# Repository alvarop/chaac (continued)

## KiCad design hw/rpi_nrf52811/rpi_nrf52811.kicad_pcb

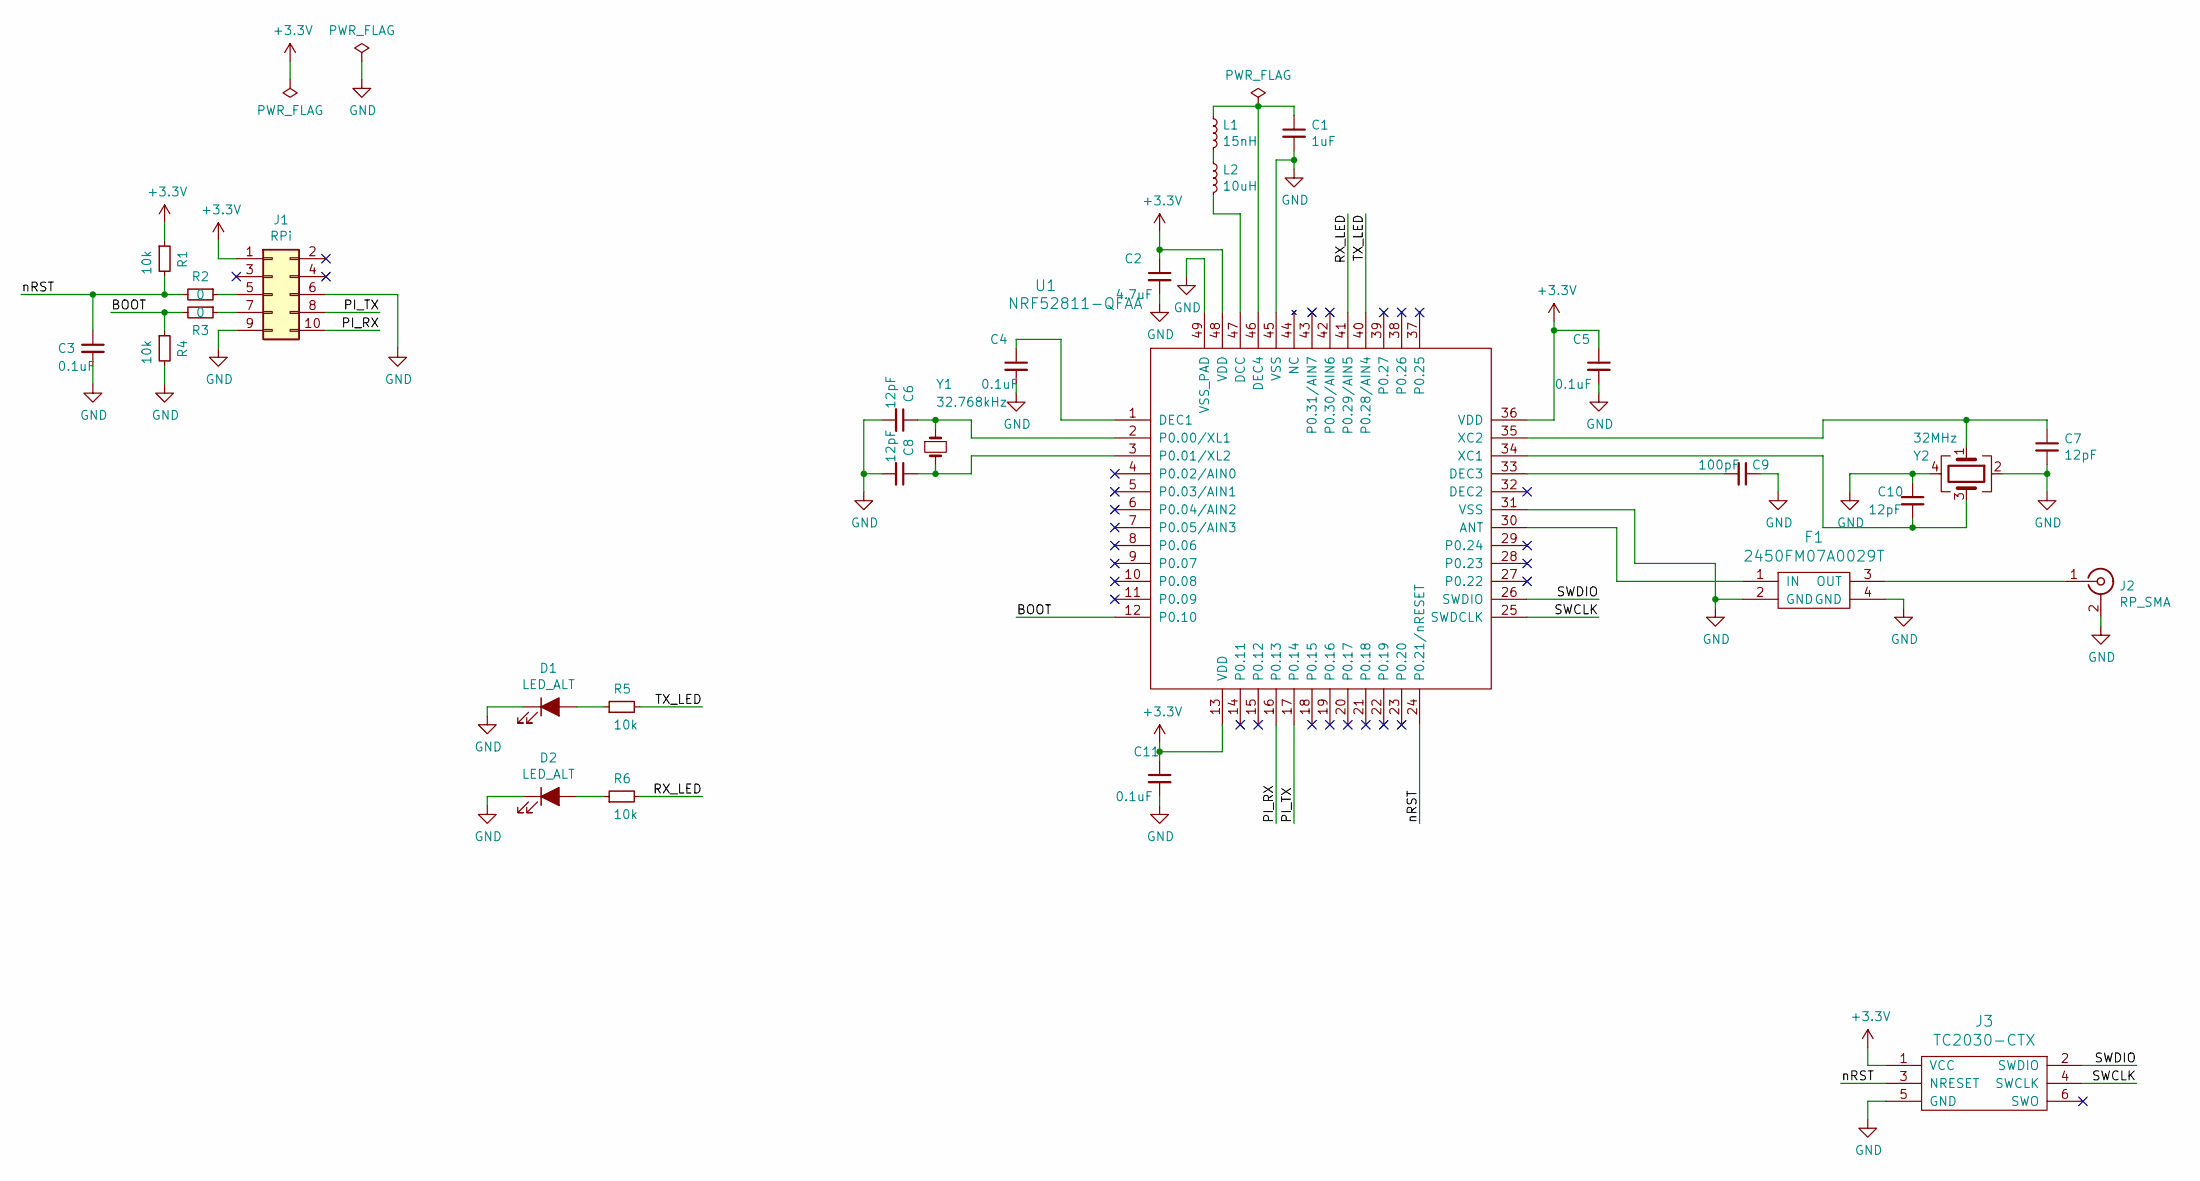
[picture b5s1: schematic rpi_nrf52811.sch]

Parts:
C1: 1uF; C_0402_1005Metric; MPN CC0402KRX5R5BB105
C2: 4.7uF; C_0603_1608Metric; MPN CL10B475KQ8NQNC
C3, C4, C5, C11: 0.1uF; C_0402_1005Metric; MPN GRM155R61A104KA01D
C6, C7, C8, C10: 12pF; C_0402_1005Metric; MPN C0402C120J5GACTU
C9: 100pF; C_0402_1005Metric; MPN UMK105CG101JV-F
D1, D2: LED_ALT; LED_0402_1005Metric; MPN QBLP595-IG
F1: 2450FM07A0029T; MPN 2450FM07A0029T
J1: RPi; PinSocket_2x05_P2.54mm_Vertical_SMD; MPN NPPC052KFMS-RC
J2: RP_SMA; SMA_Samtec_SMA-J-P-H-ST-EM1_EdgeMount; MPN CONREVSMA003.062
J3: TC2030-CTX; TC2030-NL
L1: 15nH; L_0402_1005Metric; MPN HK100515NJ-T‎
L2: 10uH; L_0603_1608Metric; MPN ‎LQM18FN100M00D‎
R1, R4, R5, R6: 10k; R_0402_1005Metric; MPN RC0402JR-0710KL
R2, R3: 0; R_0402_1005Metric; MPN RC1005J000CS
U1: NRF52811-QFAA; NRF52811-QFN48; MPN ‎NRF52811-QFAA-R‎
Y1: 32.768kHz; Crystal_SMD_3215-2Pin_3.2x1.5mm; MPN FC-135 32.7680KA-AC0
Y2: 32MHz; Crystal_SMD_2016-4Pin_2.0x1.6mm; MPN CX2016DB32000D0FLJCC

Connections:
+3V3: C2.1, C5.1, C11.1, J1.1, J3.1 (VCC), R1.1, U1.13 (VDD), U1.36 (VDD), U1.48 (VDD)
/BOOT: R3.2, R4.1, U1.12 (P0.10)
/PI_RX: J1.10, U1.16 (P0.13)
/PI_TX: J1.8, U1.17 (P0.14)
/RX_LED: R6.2, U1.41 (P0.29/AIN5)
/SWCLK: J3.4 (SWCLK), U1.25 (SWDCLK)
/SWDIO: J3.2 (SWDIO), U1.26 (SWDIO)
/TX_LED: R5.2, U1.40 (P0.28/AIN4)
/nRST: C3.1, J3.3 (NRESET), R1.2, R2.2, U1.24 (P0.21/nRESET)
GND: C1.2, C2.2, C3.2, C4.2, C5.2, C6.2, C7.2, C8.2, C9.1, C10.1, C11.2, D1.1 (K), D2.1 (K), F1.2 (GND), F1.4 (GND), J1.6, J1.9, J2.2 (Ext), J3.5 (GND), R4.2, U1.31 (VSS), U1.45 (VSS), U1.49 (VSS_PAD), Y2.2, Y2.4
unnamed: C1.1, L1.1, U1.46 (DEC4)
unnamed: C4.1, U1.1 (DEC1)
unnamed: C6.1, U1.2 (P0.00/XL1), Y1.1
unnamed: C7.1, U1.35 (XC2), Y2.1
unnamed: C8.1, U1.3 (P0.01/XL2), Y1.2
unnamed: C9.2, U1.33 (DEC3)
unnamed: C10.2, U1.34 (XC1), Y2.3
unnamed: D1.2 (A), R5.1
unnamed: D2.2 (A), R6.1
unnamed: F1.1 (IN), U1.30 (ANT)
unnamed: F1.3 (OUT), J2.1 (In)
unnamed: J1.5, R2.1
unnamed: J1.7, R3.1
unnamed: L1.2, L2.1
unnamed: L2.2, U1.47 (DCC)

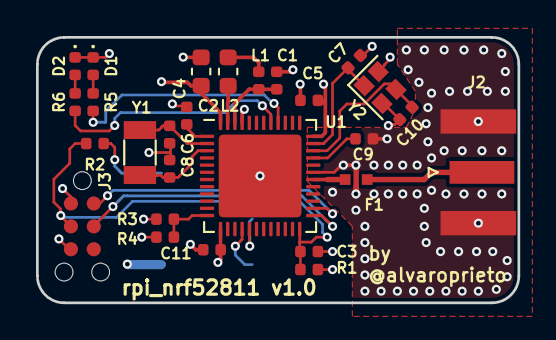
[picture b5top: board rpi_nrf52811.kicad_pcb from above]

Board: 4 copper layers, 26.8 x 14.8 mm, 28 parts (1 on the bottom side), 25 nets.

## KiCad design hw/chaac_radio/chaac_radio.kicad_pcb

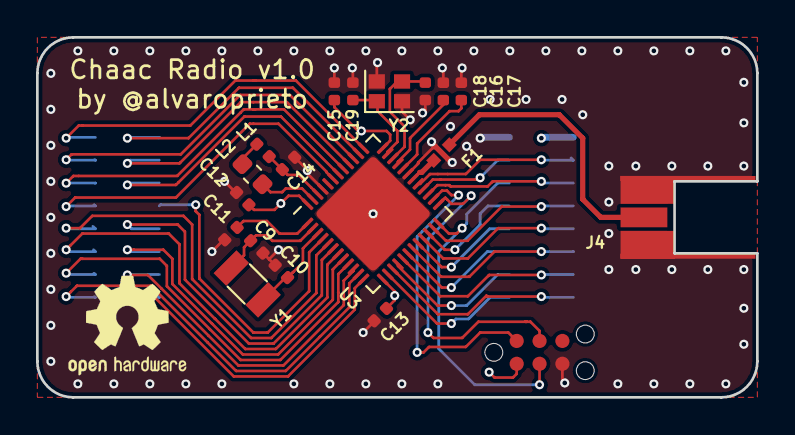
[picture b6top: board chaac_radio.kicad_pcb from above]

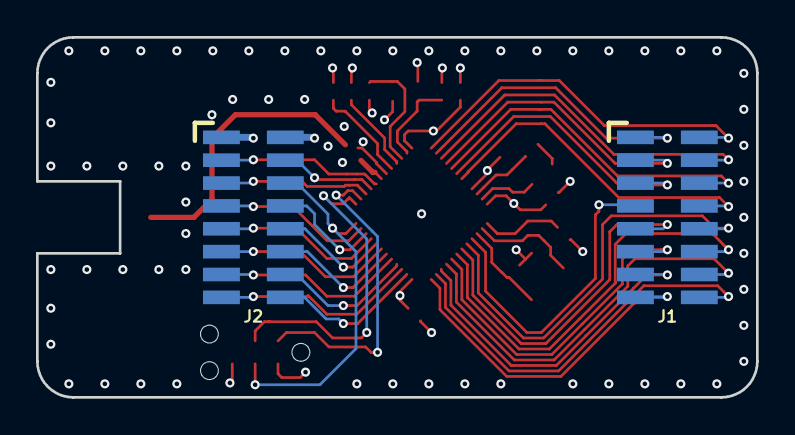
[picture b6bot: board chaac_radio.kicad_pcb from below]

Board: 4 copper layers, 40.0 x 20.0 mm, 21 parts (2 on the bottom side), 46 nets.

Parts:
C9, C10, C18, C19: 12pF; C_0402_1005Metric
C11, C13, C15: 0.1uF; C_0402_1005Metric
C12: 4.7uF; C_0402_1005Metric
C14: 1uF; C_0402_1005Metric
C16: 100pF; C_0402_1005Metric
C17: DNP; C_0402_1005Metric
F1: 2450FM07A0029T
J1, J2: 20021321-00016C4LF
J3: TC2030-CTX; TC2030-NL
J4: RP_SMA; MOLEX-0734150963
L1: 15nH; L_0402_1005Metric
L2: 10uH; L_0603_1608Metric
U3: NRF52811-QFAA; QFN-48-1EP_6x6mm_P0.4mm_EP4.6x4.6mm
Y1: 32.768kHz; Crystal_SMD_3215-2Pin_3.2x1.5mm
Y2: 32MHz; Crystal_SMD_2016-4Pin_2.0x1.6mm

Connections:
+3V3: C12.1, C13.1, C15.1, J2.1, J3.1, U3.13, U3.36, U3.48
/P0.02-AIN0: J1.7, U3.4
/P0.03-AIN1: J1.10, U3.5
/P0.04-AIN2: J1.9, U3.6
/P0.05-AIN3: J1.12, U3.7
/P0.06: J1.11, U3.8
/P0.07: J1.14, U3.9
/P0.08: J1.13, U3.10
/P0.09: J1.16, U3.11
/P0.10: J1.15, U3.12
/P0.11: J2.16, U3.14
/P0.12: J2.15, U3.15
/P0.13: J2.14, U3.16
/P0.14: J2.13, U3.17
/P0.15: J2.12, U3.18
/P0.16: J2.11, U3.19
/P0.17: J2.10, U3.20
/P0.18: J2.9, U3.21
/P0.19: J2.8, U3.22
/P0.20: J2.7, U3.23
/P0.22: J2.5, U3.27
/P0.23: J2.4, U3.28
/P0.24: J2.3, U3.29
/P0.25: J1.2, U3.37
/P0.26: J1.1, U3.38
/P0.27: J1.4, U3.39
/P0.28-AIN4: J1.3, U3.40
/P0.29-AIN5: J1.6, U3.41
/P0.30-AIN6: J1.5, U3.42
/P0.31-AIN7: J1.8, U3.43
/SWCLK: J3.4, U3.25
/SWDIO: J3.2, U3.26
/nRST: J2.6, J3.3, U3.24
GND: C9.2, C10.2, C11.2, C12.2, C13.2, C14.2, C15.2, C16.1, C17.1, C18.1, C19.2, F1.2, F1.4, J2.2, J3.5, J4.2, U3.31, U3.45, U3.49, Y2.2, Y2.4
unnamed: C9.1, U3.2, Y1.1
unnamed: C10.1, U3.3, Y1.2
unnamed: C11.1, U3.1
unnamed: C14.1, L1.1, U3.46
unnamed: C16.2, U3.33
unnamed: C17.2, U3.32
unnamed: C18.2, U3.34, Y2.3
unnamed: C19.1, U3.35, Y2.1
unnamed: F1.1, U3.30
unnamed: F1.3, J4.1
unnamed: L1.2, L2.1
unnamed: L2.2, U3.47

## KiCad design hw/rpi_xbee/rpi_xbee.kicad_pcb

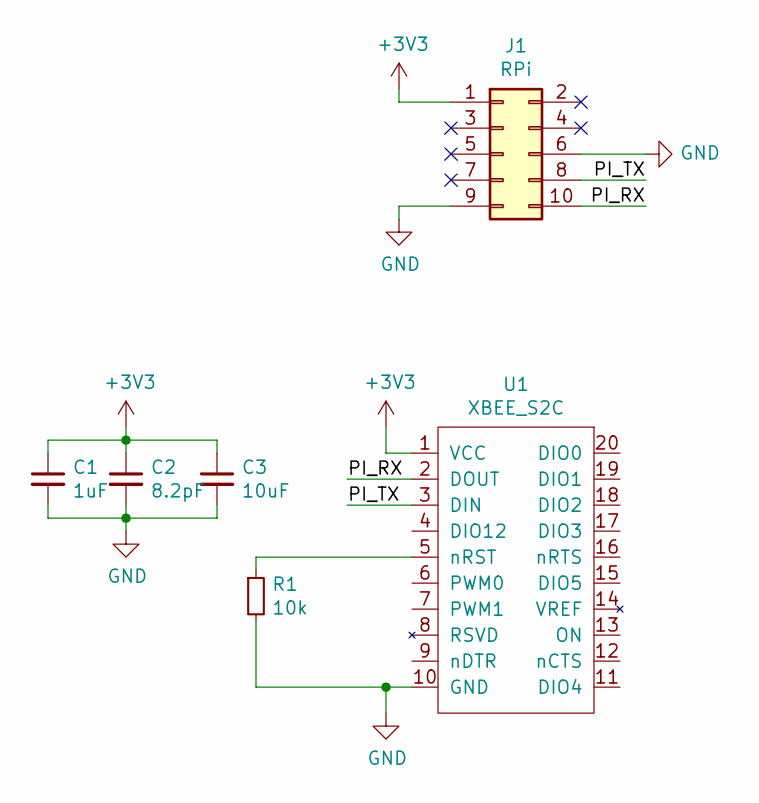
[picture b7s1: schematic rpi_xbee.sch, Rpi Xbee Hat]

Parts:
C1: 1uF; C_0603_1608Metric
C2: 8.2pF; C_0603_1608Metric
C3: 10uF; C_0603_1608Metric
J1: RPi; PinSocket_2x05_P2.54mm_Vertical
R1: 10k; R_0603_1608Metric
U1: XBEE_S2C; XBEE_S2C_TH

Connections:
+3V3: C1.1, C2.1, C3.1, J1.1, U1.1 (VCC)
/PI_RX: J1.10, U1.2 (DOUT)
/PI_TX: J1.8, U1.3 (DIN)
GND: C1.2, C2.2, C3.2, J1.6, J1.9, R1.2, U1.10 (GND)
unnamed: R1.1, U1.5 (nRST)

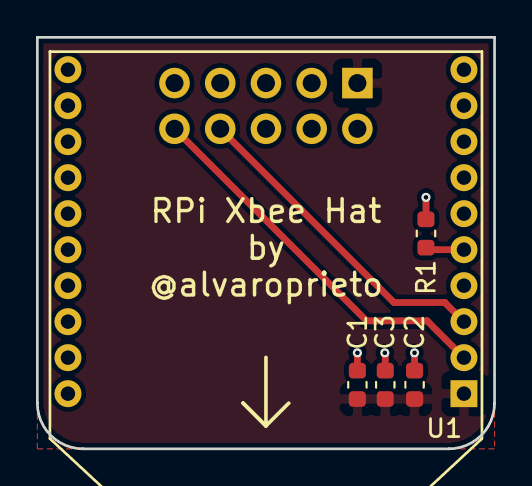
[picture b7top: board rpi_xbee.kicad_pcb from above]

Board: 2 copper layers, 25.4 x 22.9 mm, 6 parts (1 on the bottom side), 5 nets.

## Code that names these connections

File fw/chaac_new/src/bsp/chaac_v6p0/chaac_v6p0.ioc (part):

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PA0-CK_IN.GPIO_Label=WDIR
PA0-CK_IN.GPIOParameters=GPIO_Label
PA6.Mode=Full_Duplex_Master
PA15\ (JTDI).GPIOParameters=GPIO_Label
Mcu.UserName=STM32L412KBUx
PA10.GPIO_PuPd=GPIO_PULLUP
PA11.GPIOParameters=GPIO_PuPd,GPIO_Label,GPIO_ModeDefaultEXTI
PA3.GPIOParameters=GPIO_Label
PB0.GPIO_Label=RADIO_NRST
PA15\ (JTDI).Signal=GPIO_Output
PH3-BOOT0\ (BOOT0).Signal=GPIO_Output
PA11.GPIO_PuPd=GPIO_PULLUP
PC15-OSC32_OUT\ (PC15).Mode=LSE-External-Oscillator
PA2.GPIOParameters=GPIO_Label
RCC.SYSCLKSource=RCC_SYSCLKSOURCE_PLLCLK
PB5.GPIOParameters=GPIO_Label
PC14-OSC32_IN\ (PC14).Mode=LSE-External-Oscillator
PA14\ (JTCK/SWCLK).Signal=SYS_JTCK-SWCLK
PB6.Signal=I2C1_SCL
PB6.Mode=I2C
PA8.GPIOParameters=GPIO_Label
RCC.HSE_VALUE=8000000
PA0-CK_IN.Signal=ADCx_IN5
PH3-BOOT0\ (BOOT0).GPIOParameters=GPIO_Label
PB0.GPIOParameters=GPIO_Label
PA1.GPIOParameters=GPIO_Label
PB1.GPIO_Label=RADIO_BUSY
PA10.GPIO_Label=WSPEED
PB7.Signal=I2C1_SDA
PA8.Signal=GPXTI8
Mcu.Package=UFQFPN32
PB1.Signal=GPIO_Input
PA6.Signal=SPI1_MISO
PA10.GPIO_ModeDefaultEXTI=GPIO_MODE_IT_FALLING
PA2.GPIO_Label=BATT
PA10.Signal=GPXTI10
PB5.GPIO_Label=RADIO_TXEN
PA4.GPIO_Label=RADIO_CS
PA3.Signal=GPIO_Input
PA5.Mode=Full_Duplex_Master
PA7.Mode=Full_Duplex_Master
PA11.GPIO_Label=RAIN
PC15-OSC32_OUT\ (PC15).Signal=RCC_OSC32_OUT
PB4\ (NJTRST).GPIOParameters=GPIO_Label
PA8.GPIO_Label=RADIO_DIO1
PB3\ (JTDO/TRACESWO).Signal=SYS_JTDO-SWO
PA1.Signal=ADCx_IN6
PA5.Signal=SPI1_SCK
board=custom
PA1.GPIO_Label=VSOLAR
PA10.GPIOParameters=GPIO_PuPd,GPIO_Label,GPIO_ModeDefaultEXTI
PA4.GPIOParameters=GPIO_Label
PA15\ (JTDI).GPIO_Label=SNS_3V3_EN
Mcu.Name=STM32L412KBUx
PA2.Signal=ADCx_IN7
PH3-BOOT0\ (BOOT0).GPIO_Label=LED1
PA4.Signal=GPIO_Output
RCC.SYSCLKFreq_VALUE=32000000
PB5.Signal=GPIO_Output
PC14-OSC32_IN\ (PC14).Signal=RCC_OSC32_IN
PA11.Signal=GPXTI11
PB7.Mode=I2C
PB4\ (NJTRST).GPIO_Label=RADIO_RXEN
PA11.GPIO_ModeDefaultEXTI=GPIO_MODE_IT_FALLING
PB0.Signal=GPIO_Output
PA13\ (JTMS/SWDIO).Signal=SYS_JTMS-SWDIO
PA3.GPIO_Label=RADIO_DIO2
PB1.GPIOParameters=GPIO_Label
PA7.Signal=SPI1_MOSI
PB4\ (NJTRST).Signal=GPIO_Output

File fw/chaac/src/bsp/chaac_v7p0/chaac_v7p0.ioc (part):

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Mcu.Name=STM32L412KBTx
Mcu.Package=LQFP32
Mcu.UserName=STM32L412KBTx
PA0-CK_IN.GPIOParameters=GPIO_Label
PA0-CK_IN.GPIO_Label=BATT
PA0-CK_IN.Signal=ADCx_IN5
PA1.GPIOParameters=GPIO_Label
PA1.GPIO_Label=SOLAR
PA1.Signal=ADCx_IN6
PA11.Mode=Device
PA11.Signal=USB_DM
PA12.Mode=Device
PA12.Signal=USB_DP
PA13\ (JTMS/SWDIO).Mode=Serial_Wire
PA13\ (JTMS/SWDIO).Signal=SYS_JTMS-SWDIO
PA14\ (JTCK/SWCLK).Mode=Serial_Wire
PA14\ (JTCK/SWCLK).Signal=SYS_JTCK-SWCLK
PA15\ (JTDI).GPIOParameters=GPIO_Label
PA15\ (JTDI).GPIO_Label=LED2
PA15\ (JTDI).Signal=GPIO_Output
PA2.Mode=Asynchronous
PA2.Signal=LPUART1_TX
PA3.Mode=Asynchronous
PA3.Signal=LPUART1_RX
PA4.GPIOParameters=GPIO_Label
PA4.GPIO_Label=RADIO_CS
PA4.Signal=GPIO_Output
PA5.Mode=Full_Duplex_Master
PA5.Signal=SPI1_SCK
PA6.Mode=Full_Duplex_Master
PA6.Signal=SPI1_MISO
PA7.Mode=Full_Duplex_Master
PA7.Signal=SPI1_MOSI
PA8.GPIOParameters=GPIO_Label
PA8.GPIO_Label=RADIO_DIO1
PA8.Signal=GPXTI8
PA9.GPIOParameters=GPIO_Label
PA9.GPIO_Label=RADIO_DIO2
PA9.Signal=GPIO_Input
PB0.GPIOParameters=GPIO_Label
PB0.GPIO_Label=RS232_EN
PB0.Signal=GPIO_Output
PB1.GPIOParameters=GPIO_Label
PB1.GPIO_Label=NINVALID
PB1.Signal=GPIO_Input
PB3\ (JTDO/TRACESWO).GPIOParameters=GPIO_Label
PB3\ (JTDO/TRACESWO).GPIO_Label=LED1
PB3\ (JTDO/TRACESWO).Signal=GPIO_Output
PB4\ (NJTRST).GPIOParameters=GPIO_Label
PB4\ (NJTRST).GPIO_Label=RADIO_RXEN
PB4\ (NJTRST).Signal=GPIO_Output
PB5.GPIOParameters=GPIO_Label
PB5.GPIO_Label=RADIO_TXEN
PB5.Signal=GPIO_Output
PB6.GPIOParameters=GPIO_Label
PB6.GPIO_Label=RADIO_NRST
PB6.Signal=GPIO_Output
PB7.GPIOParameters=GPIO_Label
PB7.GPIO_Label=RADIO_BUSY
PB7.Signal=GPIO_Input
PC14-OSC32_IN\ (PC14).Mode=LSE-External-Oscillator
PC14-OSC32_IN\ (PC14).Signal=RCC_OSC32_IN
PC15-OSC32_OUT\ (PC15).Mode=LSE-External-Oscillator
PC15-OSC32_OUT\ (PC15).Signal=RCC_OSC32_OUT
RCC.HSE_VALUE=8000000
RCC.SYSCLKFreq_VALUE=32000000
RCC.SYSCLKSource=RCC_SYSCLKSOURCE_PLLCLK
board=custom

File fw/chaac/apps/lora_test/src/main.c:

#include <assert.h>
#include <string.h>

#include "sysinit/sysinit.h"
#include "os/os.h"
#include "console/console.h"
#include "bsp/bsp.h"
#include "hal/hal_gpio.h"

#include <packet/packet.h>
#include <raw_uart/raw_uart.h>

#include "radio/radio.h"
#include "sx126x/sx126x.h"
#include "chaac_packet.h"

#define RF_FREQUENCY 915000000

#define TX_OUTPUT_POWER 14

#define LORA_BANDWIDTH                              0         // [0: 125 kHz,
                                                              //  1: 250 kHz,
                                                              //  2: 500 kHz,
                                                              //  3: Reserved]
#define LORA_SPREADING_FACTOR                       7         // [SF7..SF12]
#define LORA_CODINGRATE                             1         // [1: 4/5,
                                                              //  2: 4/6,
                                                              //  3: 4/7,
                                                              //  4: 4/8]
#define LORA_PREAMBLE_LENGTH                        8       // Same for Tx and Rx
#define LORA_SYMBOL_TIMEOUT                         0       // Symbols
#define LORA_FIX_LENGTH_PAYLOAD_ON                  false
#define LORA_IQ_INVERSION_ON                        false


#define RX_TIMEOUT_VALUE                            0
#define BUFFER_SIZE                                 64 // Define the payload size her

uint8_t txbuff[BUFFER_SIZE];
   
static RadioEvents_t RadioEvents;

void packet_tx_fn(int16_t len, void* data) {

#if HW_VERSION == 0
    hal_gpio_init_out(RX_LED_PIN, 1);
#endif
    
    raw_uart_tx(len, data);

#if HW_VERSION == 0
    hal_gpio_init_out(RX_LED_PIN, 0);
#endif
}

void OnTxDone( void )
{
    Radio.Standby( );
}

void OnRxDone( uint8_t *payload, uint16_t size, int16_t rssi, int8_t snr )
{
    const uint16_t total_size = size + sizeof(chaac_lora_rxinfo_t);
    if(total_size <= BUFFER_SIZE) {
        memcpy(txbuff, payload, size);
    
        chaac_lora_rxinfo_t *footer = (chaac_lora_rxinfo_t *)&txbuff[size];
        footer->rssi = rssi;
        footer->snr = snr;

        packet_tx(size + sizeof(chaac_lora_rxinfo_t), txbuff);
        /*for(uint16_t byte = 0; byte < size; byte++) {
            console_printf("%02X ", payload[byte]);
        }
        console_printf("RSSI:%d SNR:%d\n", rssi, snr);
        */
        Radio.Rx(RX_TIMEOUT_VALUE);
    }
}

void OnTxTimeout( void )
{
    Radio.Standby( );
}

void OnRxTimeout( void )
{   
    //console_printf("RX Timeout\n");
    /*Radio.Standby( );*/
    Radio.Rx( RX_TIMEOUT_VALUE );   //  Restart Rx
}

void OnRxError( void )
{
    /*console_printf("RX Err\n");*/
    /*Radio.Standby( );*/
    Radio.Rx( RX_TIMEOUT_VALUE );   //  Restart Rx
}

int init_radio(void) {
    /*console_printf("Initializing radio\n");*/

#if HW_VERSION == 0
    hal_gpio_init_out(TX_LED_PIN, 0);
    hal_gpio_init_out(RX_LED_PIN, 0);
#endif

    RadioEvents.TxDone = OnTxDone;
    RadioEvents.RxDone = OnRxDone;
    RadioEvents.TxTimeout = OnTxTimeout;
    RadioEvents.RxTimeout = OnRxTimeout;
    RadioEvents.RxError = OnRxError;
//    RadioEvents.CadDone = OnCadDone;

    /*console_printf("Radio.Init\n");*/
    Radio.Init( &RadioEvents );

    /*console_printf("Radio.SetTxConfig\n");\*/
    Radio.SetTxConfig( MODEM_LORA, TX_OUTPUT_POWER, 0, LORA_BANDWIDTH,
                                   LORA_SPREADING_FACTOR, LORA_CODINGRATE,
                                   LORA_PREAMBLE_LENGTH, LORA_FIX_LENGTH_PAYLOAD_ON,
                                   true, 0, 0, LORA_IQ_INVERSION_ON, 3000 );

    Radio.SetRxConfig( MODEM_LORA, LORA_BANDWIDTH, LORA_SPREADING_FACTOR,
                                   LORA_CODINGRATE, 0, LORA_PREAMBLE_LENGTH,
                                   LORA_SYMBOL_TIMEOUT, LORA_FIX_LENGTH_PAYLOAD_ON,
                                   0, true, 0, 0, LORA_IQ_INVERSION_ON, true );

       return 0;
}

#define BLINK_TASK_PRI         (99)
#define BLINK_STACK_SIZE       (64)
struct os_task blink_task;
os_stack_t blink_task_stack[BLINK_STACK_SIZE];



void blink_task_fn(void *arg) {

    hal_gpio_init_out(STATUS_LED_PIN, 0);

    while(1) {
        os_time_delay(OS_TICKS_PER_SEC);
        hal_gpio_toggle(STATUS_LED_PIN);
    }

}

int
main(int argc, char **argv)
{
    sysinit();

    raw_uart_init(NULL);
    packet_init_tx_fn(packet_tx_fn);

    os_task_init(
        &blink_task,
        "blink_task",
        blink_task_fn,
        NULL,
        BLINK_TASK_PRI,
        OS_WAIT_FOREVER,
        blink_task_stack,
        BLINK_STACK_SIZE);

    init_radio();

    Radio.Rx(RX_TIMEOUT_VALUE);

    while(1) {
        os_eventq_run(os_eventq_dflt_get());
    }

    assert(0);

    return 0;
}

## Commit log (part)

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2019-02-02 Switching to 4MHz clock and regulator range 2.
    This gets us from 2.5mA to ~1mA avg running current.
    Nothing close to what it could be, but still an improvement
2019-02-03 Start plotting bar charts for rain!
2019-02-07 Add baud rate to mcumgr and change mtu
2019-02-07 Change xbee uart speed to 19200
2019-02-08 Adding workaround for raspberry pi serial flush
2019-02-08 Add specific bootloader packet
2019-02-09 Don't have a fan anymore
2019-02-09 Bootloader update!
    If the user uses the boot button during reset, the debug UART
    will be used for the bootloader.
    If the boot pin is not asserted during boot, the xbee uart will be
    used instead.
2019-02-09 forgot to add hal_bsp!
2019-02-13 Fix update script
2019-02-19 Adding an hour to catch the current hour for rain data
2019-02-19 Use datetime to round instead of timestamp for a bit more clarity
2019-02-21 Use localStorage to keep pressure units
    Start converting pressure units in Plots!
    TODO: Add nicer way to switch between units
2019-02-22 Use modal for settings and add temperature
    TODO - temperature plot scaling
2019-05-16 Switched status page to load from json instead of through flask template
    Added hostname
2019-05-17 Minor filename fixes
2019-05-17 Make sure requests gets installed
2019-05-17 Update list layout
2019-05-17 Don't nuke nginx conf everytime we run support/update.sh
2019-05-23 Released chaac v2.0 to JLCPCB
2019-05-25 Released nrf52811_usb to oshpark :D
2019-05-29 Make code a bit more flexible (MCU wise)
2019-05-30 Need to relocate NVIC otherwise this won't work with bootloader
2019-05-30 Enable uart
2019-05-30 BMP280 and AM2315 both seem to be working :D
2019-05-31 XBEE now working :D
2019-05-31 adding chaac-dev to server
2019-06-01 Started schematic/layout on nrf52811_breakout
2019-06-02 renamed nrf51822_breakout to chaac_radio
    Fixed up some via alignment and stitching
2019-06-02 Done routing chaac v3.0 base board?
2019-06-02 Fixed DRC errors and added url
2019-06-02 Removed chaac radio from chaac and used 2 connectors
    Ordered chaac radio from JLCPCB
    Ordered chaac from oshpark
2019-06-09 renamed radio/packet to serial/packet
2019-06-09 Modify windrain to get directions and degrees
2019-06-09 adding chaac logger ble!
2019-06-09 minor fix to chaac frontend
2019-06-10 more frontend fixes
2019-06-10 Change index->sample for consistency
2019-06-10 Python formatting
2019-06-15 Fix hw version definition and rain pin on chaacv3
2019-06-15 Don't print stuff out!
2019-06-17 forgot to update server
2019-09-19 Minor chaac server tweaks
2019-09-23 Enable cache results for chaac_server
2019-09-23 Adding default config as well as updating setup.sh
2019-09-23 Using the correct path this time
2019-09-23 Minor supervisor change for chaac_cache
2019-10-01 Started writing BME280 driver
2019-10-01 more updatest to bme280 driver
2019-10-02 minor fixes to bme280 driver. It compiles now :D Still untested
2019-10-04 Fixed hw version in bsp and change beacon magic to work again
2019-10-07 Don't need these anymore
2019-10-13 Add uid to downsampling
2019-11-01 Fix data de-duplication bug
2019-11-23 Created db backup script!
2019-11-23 Removed day length stuff
2019-11-23 Trying out no pipenv
2019-11-23 use pip3
2019-11-23 install serial packet
2019-11-23 minor stats fix
2019-11-24 Specify a uid for all db reads (default to last sample)
2019-11-24 Adding stats page!
2019-11-24 minor tweak to compute stats
2020-02-20 chaacdb updates
2020-06-10 Don't worry about venvs
2020-06-10 Updating readme
2020-06-16 Finished chaac v4.0!
2020-06-20 Adding blinky usb app
2020-06-21 Fix part number for U2
2020-06-21 Added lora/sx126x drivers
2020-06-21 Added lora_test app with sample code
2020-06-22 Finally have LoRa rx working
    Removing LORA_SYMBOL_TIMEOUT seems to help receive all the packets :D
2020-06-24 Add chaac v4.0 bsp
2020-06-25 Fix simple_adc_nrf528xx.c to work with new nrfx 2.1 libs
2020-06-25 Start working on controller_lora
2020-06-29 Fix chaac v4.0 bsp
2020-06-29 Adding new packet format in python
2020-06-29 Added header to WeatherPacketV1P0 and added LoraRxInfo packet
2020-06-29 Start forwarding chaac packets over uart in lora_test app
2020-06-30 Change radio driver to event driven Irq processing
2020-06-30 change lora_test to event driven radio processing instead of polling
2020-07-21 Switch os timer in chaac v4p0 bsp
2020-07-31 Adding lora_power app and various python scrip updates
    Mostly to test range
2020-08-16 Adding nordic dev board target
2020-08-16 This is currently working fine on nrf dev board
2020-08-18 Seems to be transmitting ok now (no uart)
2020-08-24 Adding chaac v5.0
2020-08-29 Adding SX126X_USE_TCXO flag
2020-08-29 Getting rid of app_shell test app
2020-08-29 Adding initial chaac v5.0 code (untested!)
2020-09-01 Updated nrf5281x_usb_lora to be smaller
2020-09-12 ignore pycache dirs
2020-09-12 Get rid of TCXO init, since it's now done in Radio.Init
2020-09-20 Update windrain driver to work with chaac v5
    Fix windraincalc script
2020-09-23 Remove misspelled syscfg
2020-09-23 Make sure we don't sample wind sensor if it isn't there
2020-09-23 Add support for packet decoding and button packet in mqtt client
2020-10-04 Moving lora_mqtt_client to separate dir
2020-10-15 don't auto update/upgrade apt
2020-10-16 Fixed chaac lora pressure!
    Value was being sent as unsigned int 16, if pressure was below
    1000.00 hPa, it would report inaccurately.
    Noticed this because Sunbright is above sea level and was reading
    values such as 1619.68 hPa instead of 960something.
2020-10-17 Adding sketchy sample detection
    There seem to be issues with the LoRa radios.
    Sometimes data arrives a bit wrong. I'm guessing
    the data might be getting corrupted.
    Until I can add CRC to fw and update field units,
    I'll try to detect "sketchy" samples and save them
    in a separate table for later analysis.
2020-10-17 Adding descriptive sketchy message
2020-11-27 Add cubemx bsp
2020-11-27 First cmake attempt
2020-11-27 Re-did layout for chaac v6
2020-12-05 Cleaned up chaac layout
2020-12-20 Update part numbers?
2020-12-20 Blinky working with chaac v6 :D
2020-12-25 Switch from make to ninja for fun
2020-12-25 Start using freeRTOS
2020-12-25 Make sure device is reset before flashing
    This makes sure that we can flash even if device is in WFI
2020-12-26 SHT3x seems to work now :D
2020-12-27 Clean up main
2020-12-27 Basic ADC working :D
2020-12-27 change lib names
2020-12-27 Adding windrain driver :D
2020-12-29 Not sure why lpmtick wasn't working. Back to systick for now
2020-12-29 Add radio gpio's to radio test
2020-12-29 Sending and receiving now working :D
2020-12-30 Make radioirq task higher priority and use task notifications
2020-12-30 Get basic chaac packet transmitting
2020-12-31 Make sure we can flash parts in stop mode
2020-12-31 Add malloc failed and stack overflow hooks
2021-01-09 Forgot to commit some changes to pcb
2021-01-24 Adding lora_usb bsp and blinky
2021-01-24 Got very basic usb tx working
2021-01-25 Got basic rx working with echo
2021-03-06 Committing chaac v6.1 files I forgot to :(
2021-03-28 Make sure we can reset in LPM and added debug_reset
2021-03-28 Change windrain to take in ADC value to remove ADC dependency
2021-05-16 Adding antenna test board (ordered from oshpark)
2021-07-03 Changed resistors for charger to get 200mA charge rate
2021-07-03 Don't use lptimtick for usb projects
2021-07-03 Enable CRC checking for chaac and lora_usb
2021-07-03 Added sensor averaging and wind gust measurements!
2021-07-05 clean up and try docker
2021-07-07 This one seems to work on the rpi! (gunicorn/flask only, no nginx yet)
2021-07-08 Bump jinja2 from 2.11.2 to 2.11.3 in /sw/chaac_frontend/flask
    Bumps [jinja2](https://github.com/pallets/jinja) from 2.11.2 to 2.11.3.
    - [Release notes](https://github.com/pallets/jinja/releases)
    - [Changelog](https://github.com/pallets/jinja/blob/main/CHANGES.rst)
    - [Commits](https://github.com/pallets/jinja/compare/2.11.2...2.11.3)
    ---
    updated-dependencies:
2021-07-08 Move some files around
2021-07-08 swapped the files....
2021-07-08 Add /zipdb feature
2021-07-10 Add multi-device support for get_latest_sample
2021-07-11 Make plots multi-device!
2021-07-11 Got chaac-cache and chaac-server working with docker
2021-07-11 change config method and add a bunch of callbacks
2021-07-12 Reset packets now working!
2021-07-18 Wind average direction seems to be working!
2021-07-18 Try to fix files redirect
2021-07-18 Got nginx-only proxy almost working :D
2021-07-18 Quick fix to make urls relative
2021-07-18 update proxy urls to match current server
2021-07-18 Do basic caching
2021-07-21 Try out timezone stuff
2021-07-22 Proxy working, I think? Minus SSL
2021-07-22 Retire old chaac fw, chaac_new->chaac
2021-07-23 Very basic memfault working :D
2021-07-23 Fix chaac logger
2021-07-23 Rename test to chaac
2021-07-24 *almost* working
2021-07-25 Add chaac_rename script
2021-07-26 Forgot a couple
2021-07-27 Switching to hour/minutes
2021-07-27 Updating chaac to 1.0.0
2021-07-29 JK, that didn't work. 🤦‍♂️
    Changing chaac to take both wind_dir and wind_dir_deg
2021-07-29 Actually fix wind dir issue
2021-07-29 Adding upgrade_db script
2021-07-29 Clean up chaac.network index
2021-08-01 Make sure lora_usb_rx goes into rx mode after an rx error 🤦‍♂️
    Also added way of getting memfault data from usb_lora
2021-08-01 Fix db and don't plot rainless samples
2021-11-03 Add a few more checks to upgrade_db
2022-06-22 Bump numpy from 1.21.0 to 1.22.0 in /sw/chaac_frontend
    Bumps [numpy](https://github.com/numpy/numpy) from 1.21.0 to 1.22.0.
    - [Release notes](https://github.com/numpy/numpy/releases)
    - [Changelog](https://github.com/numpy/numpy/blob/main/doc/HOWTO_RELEASE.rst)
    - [Commits](https://github.com/numpy/numpy/compare/v1.21.0...v1.22.0)
    ---
    updated-dependencies:
2022-12-09 Bump certifi from 2021.5.30 to 2022.12.7 in /sw/chaac_frontend
    Bumps [certifi](https://github.com/certifi/python-certifi) from 2021.5.30 to 2022.12.7.
    - [Release notes](https://github.com/certifi/python-certifi/releases)
    - [Commits](https://github.com/certifi/python-certifi/compare/2021.05.30...2022.12.07)
    ---
    updated-dependencies:
    - dependency-name: certifi
2024-07-01 Start working on Chaac ng!
    Schematic mostly done, layout in progress
2024-07-06 More layout/routing
2024-07-15 Start parsing values :D
2024-07-20 Fix BMP script to work with latest firmware
2024-07-20 USB forwarding seems to be working :D
2024-07-22 Released v7.1 to JLCPCB
2024-07-25 minor fix for modern python
2024-07-25 Fix ADC reference voltage
2024-07-25 Start moving vaisala parser to fw
2024-07-26 Fix humidity
2024-08-01 Start handling rain (untested)
2024-08-06 Forgot to multiply by 10 🤦‍♂️
2024-11-16 Maybe fix Sunbright IP address?
2026-04-12 Start working on cloudflare migration
